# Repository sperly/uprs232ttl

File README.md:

# uprs232ttl
TTL Serial Adapter for C64/C128 UserPort.

The adapter is based on a non-inverting cmos buffer chip, CD4050. Following signals are used from the C64/C128:
```
FLAG <- RX (via a jumper)
PB0  <- RX
PB1  -> RTS
PB6  <- CTS
PA2  -> TX
```

There are also jumpers to switch signal path to enable null-modem communication. The default position is marked on pcb and it set for null-modem communication.
```
J4:

 RX/TX
| o o |         Null-Modem
| o o |
  o o

 RX/TX
  o o           Controller-Peripheral
| o o |
| o o |

J5:

CTS/RTS
| o o |         Null-Modem
| o o |
  o o

CTS/RTS
  o o           Controller-Peripheral
| o o |
| o o |

```

The serial output is pin compatible with common serial-usb adapters:
```
1 - GND
2 - CTS
3 - VCC
4 - TX
5 - RX
6 - DTR

```

Jumper 1 is used for enabeling RX interupt on the C64/C128. And jumper 2 is enabeling power thru the serial adapter.
```
J1:

RX Int
| o |         RX interupt enabled
| o |

RX Int
  o           RX interupt disabled
  o 

J2:

 Pwr
| o |         Power feed from C64/C128 enabled
| o |

 Pwr
  o           Power feed from C64/C128 disabled
  o 

```

Top side of pcb:

Bottom side of pcb, also containing info on jumper settings:

Case with pcb:

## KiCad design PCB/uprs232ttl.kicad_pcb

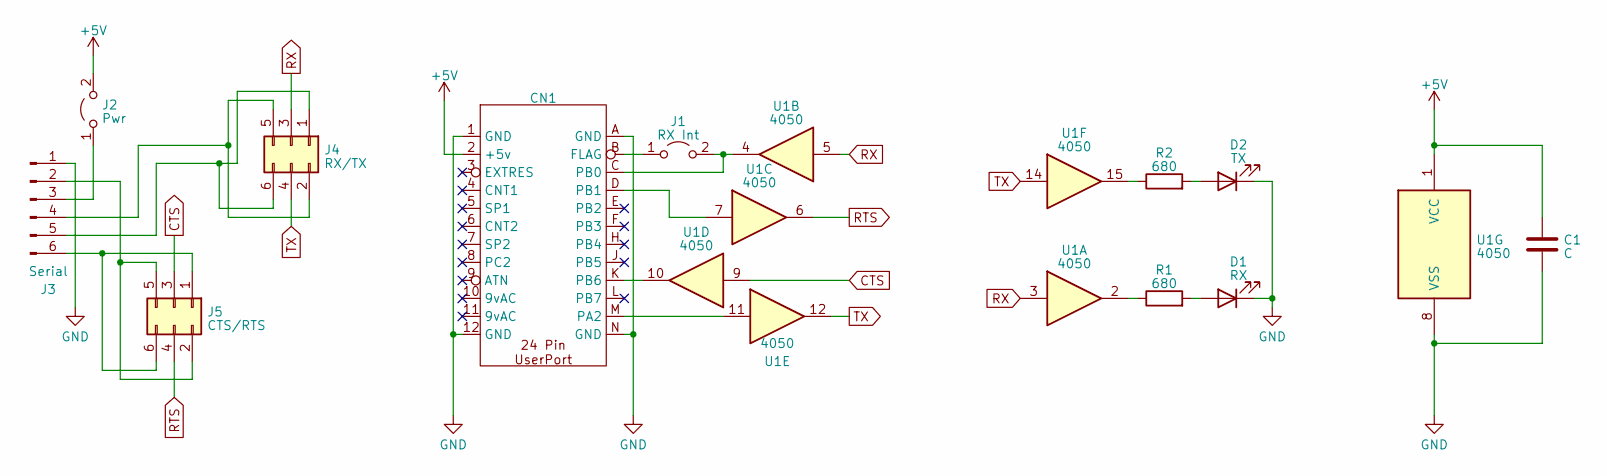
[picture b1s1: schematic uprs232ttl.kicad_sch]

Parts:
C1: C; CP_Radial_D4.0mm_P1.50mm
CN1: userport_cbm
D1: RX; LED_D3.0mm
D2: TX; LED_D3.0mm
J1: RX Int; PinHeader_1x02_P2.54mm_Vertical
J2: Pwr; PinHeader_1x02_P2.54mm_Vertical
J3: Serial; PinHeader_1x06_P2.54mm_Horizontal
J4: RX/TX; PinHeader_2x03_P2.54mm_Vertical
J5: CTS/RTS; PinHeader_2x03_P2.54mm_Vertical
R1, R2: 680; R_Axial_DIN0207_L6.3mm_D2.5mm_P10.16mm_Horizontal
U1: 4050; DIP-16_W7.62mm_Socket

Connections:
+5V: C1.1, CN1.2 (+5v), J2.2 (B), U1.1 (VCC)
CTS: J5.3, U1.9
GND: C1.2, CN1.1 (GND), CN1.12 (GND), CN1.A (GND), CN1.N (GND), D1.1 (K), D2.1 (K), J3.1, U1.8 (VSS)
unnamed: CN1.B (FLAG), J1.1 (A)
unnamed: CN1.M (PA2), U1.11
unnamed: CN1.C (PB0), J1.2 (B), U1.4
unnamed: CN1.D (PB1), U1.7
unnamed: CN1.K (PB6), U1.10
unnamed: D1.2 (A), R1.2
unnamed: D2.2 (A), R2.2
unnamed: J2.1 (A), J3.3
unnamed: J3.2, J5.2, J5.5
unnamed: J3.4, J4.2, J4.5
unnamed: J3.5, J4.1, J4.6
unnamed: J3.6, J5.1, J5.6
unnamed: R1.1, U1.2
unnamed: R2.1, U1.15
RTS: J5.4, U1.6
RX: J4.3, U1.3, U1.5
TX: J4.4, U1.12, U1.14

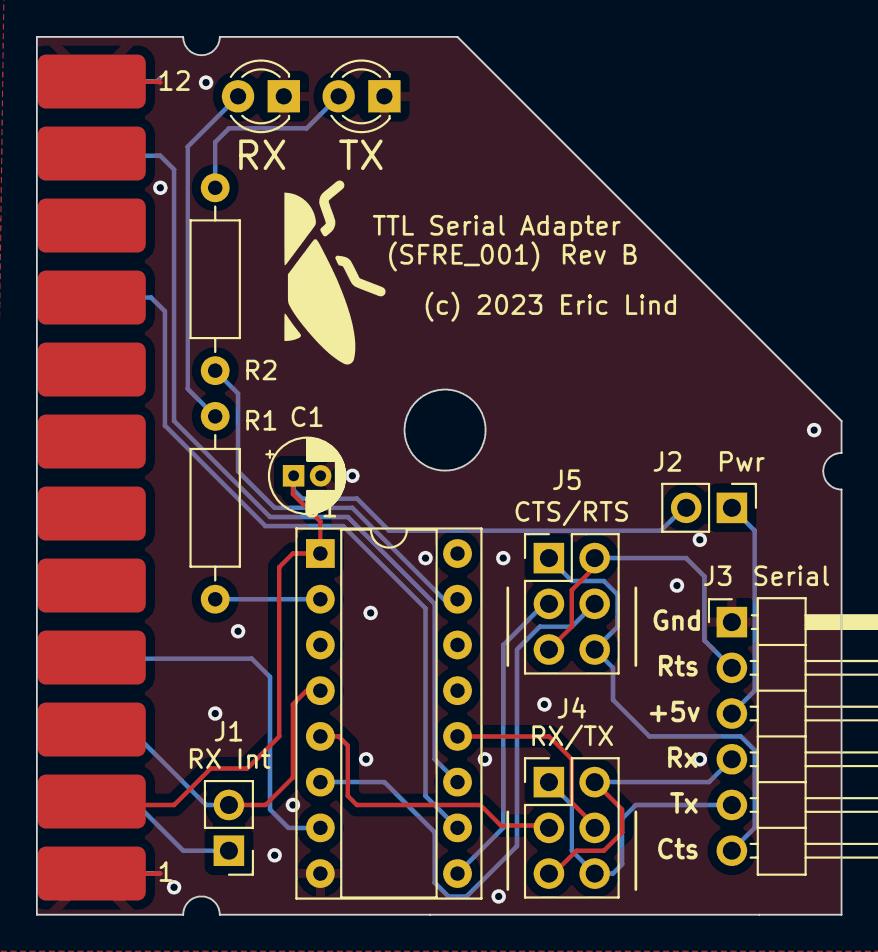
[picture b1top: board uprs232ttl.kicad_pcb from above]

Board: 2 copper layers, 44.7 x 48.8 mm, 12 parts (0 on the bottom side), 20 nets.

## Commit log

2023-08-12 Added case, pcb and userport component
2023-08-12 Added a bottom view of pcb.
2023-08-12 Added a case image and more description in README
2023-08-12 Updated image sizes.
2023-08-12 Create .gitignore for pcb folder
2023-08-12 Drop files from .gitignore
2023-08-12 Updated board name

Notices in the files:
PCB/uprs232ttl.kicad_pcb:
(c) 2023 Eric Lind
